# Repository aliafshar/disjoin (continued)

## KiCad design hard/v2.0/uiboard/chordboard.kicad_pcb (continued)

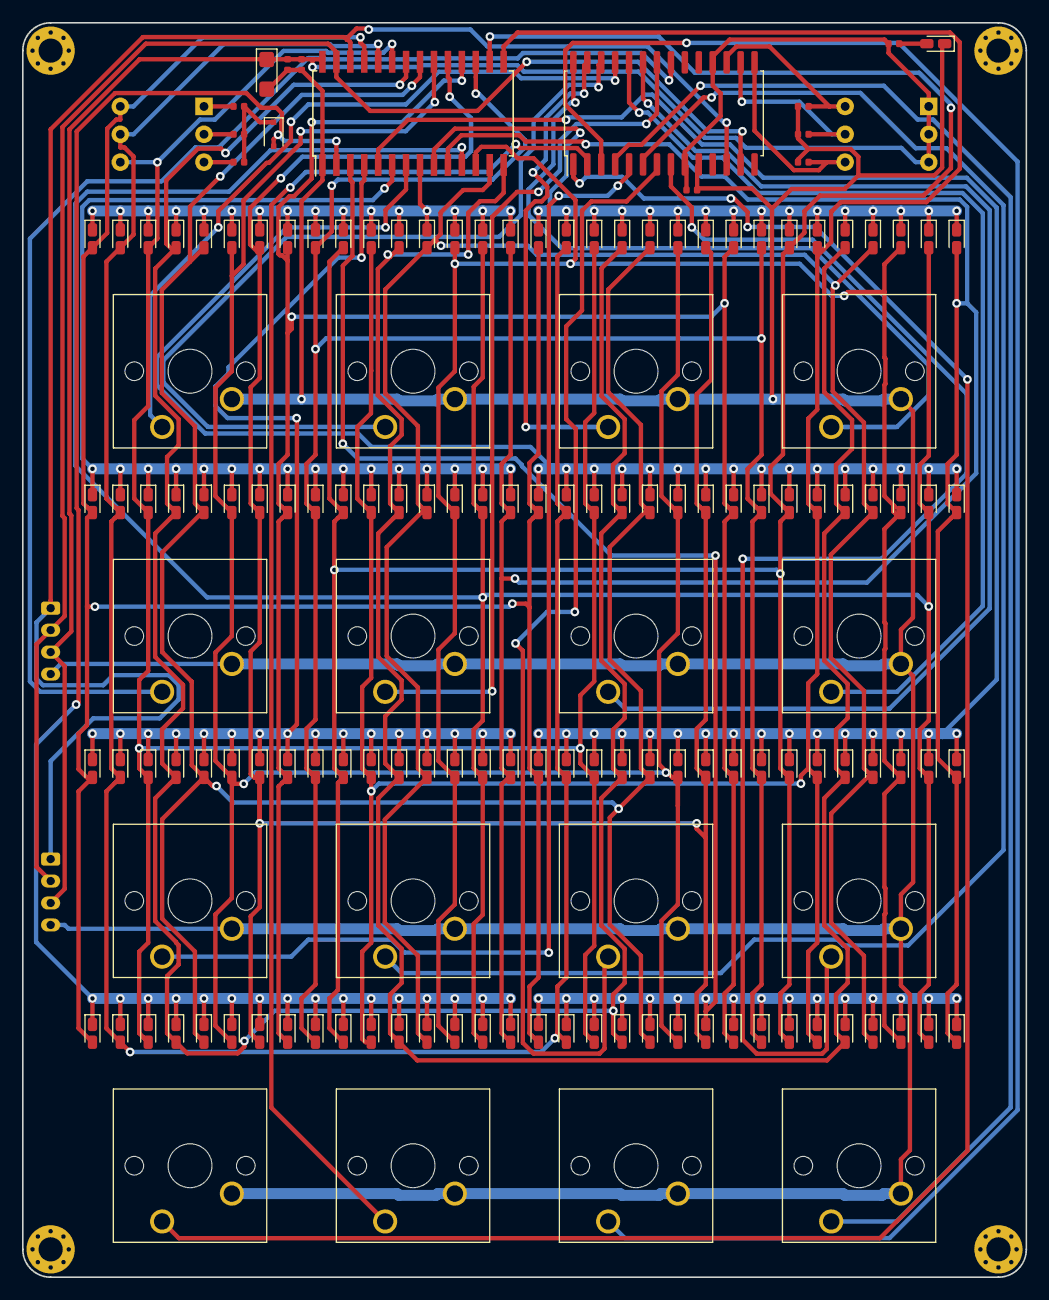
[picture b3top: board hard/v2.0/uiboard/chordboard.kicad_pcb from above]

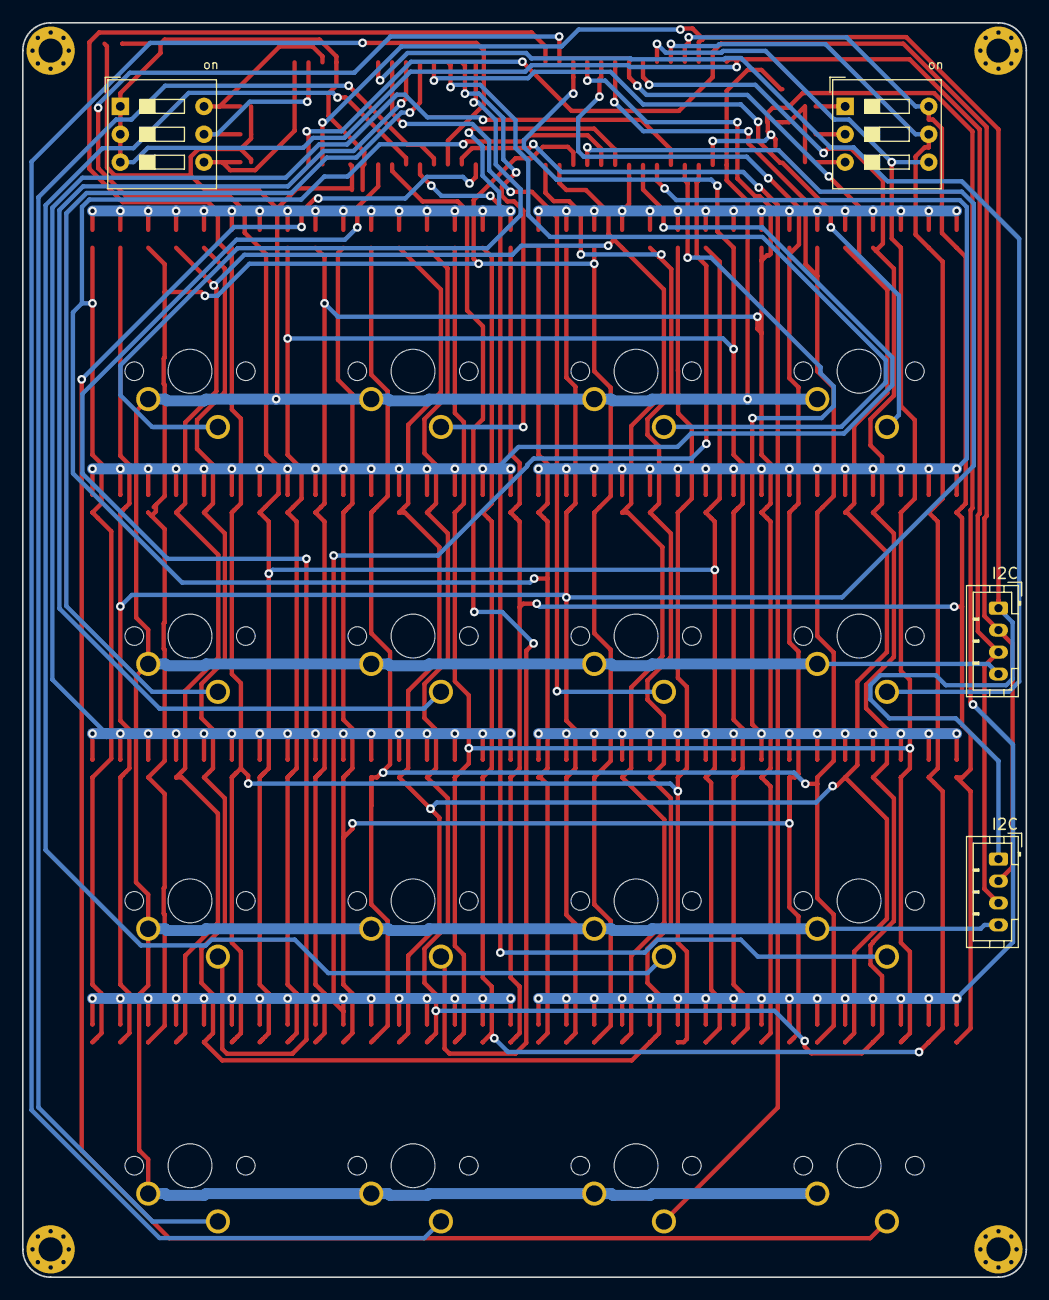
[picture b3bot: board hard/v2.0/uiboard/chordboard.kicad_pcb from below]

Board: 2 copper layers, 91.4 x 114.3 mm, 167 parts (4 on the bottom side), 52 nets.

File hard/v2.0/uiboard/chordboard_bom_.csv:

Component,Description,Part,References,Value,Footprint,Quantity Per PCB,Datasheet,LSCS
1,Polarized capacitor,CP_10uF,C4,CP_10uF,CP_EIA-3216-18_Kemet-A,1,~,C7171
2,Unpolarized capacitor,C_0.1uF,C1 C2 C3,C_0.1uF,C_0402_1005Metric,3,~,C1525
3,Diode,D_1N4148WS,D129,D_1N4148WS,D_SOD-323F,1,~,C2128
4,Light emitting diode,LED_RED,D1 D2 D3 D4 D5 D6 D7 D8 D9 D10 D11 D12 D13 D14 D15 D16 D17 D18 D19 D20 D21 D22 D23 D24 D25 D26 D27 D28 D29 D30 D31 D32 D33 D34 D35 D36 D37 D38 D39 D40 D41 D42 D43 D44 D45 D46 D47 D48 D49 D50 D51 D52 D53 D54 D55 D56 D57 D58 D59 D60 D61 D62 D63 D64 D65 D66 D67 D68 D69 D70 D71 D72 D73 D74 D75 D76 D77 D78 D79 D80 D81 D82 D83 D84 D85 D86 D87 D88 D89 D90 D91 D92 D93 D94 D95 D96 D97 D98 D99 D100 D101 D102 D103 D104 D105 D106 D107 D108 D109 D110 D111 D112 D113 D114 D115 D116 D117 D118 D119 D120 D121 D122 D123 D124 D125 D126 D127 D128 PLED1,LED_RED,LED_0603_1608Metric_Castellated,129,~,C2286
5,,HT16K33,HT1,HT16K33,SOIC-28W_7.5x17.9mm_P1.27mm,1,,C87502
6,Resistor,R_10K,R1 R2 R3 R4 R5 R6,R_10K,R_0402_1005Metric,6,~,C25744
7,Resistor,R_330R,R7,R_330R,R_0402_1005Metric,1,~,C25104
8,"16-bit I/O expander, I2C, interrupts, w pull-ups, SOIC-28",MCP23017_SO,U1,MCP23017_SO,SOIC-28W_7.5x17.9mm_P1.27mm,1,http://ww1.microchip.com/downloads/en/DeviceDoc/20001952C.pdf,C47023

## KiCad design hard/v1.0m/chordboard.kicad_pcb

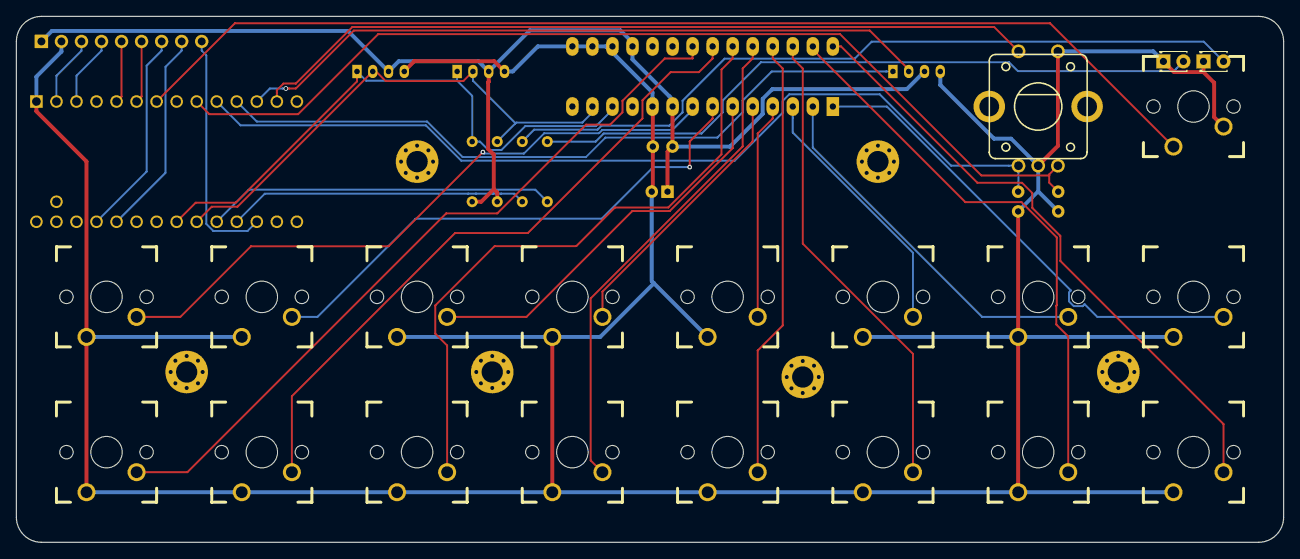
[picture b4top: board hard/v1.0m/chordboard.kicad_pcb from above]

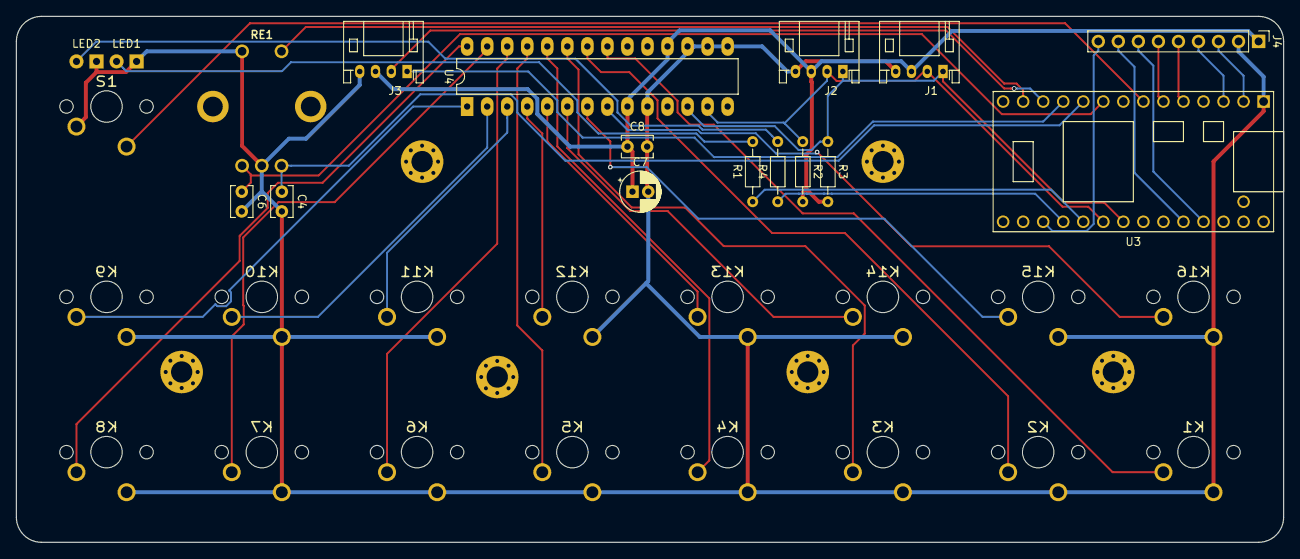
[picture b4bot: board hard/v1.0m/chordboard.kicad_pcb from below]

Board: 2 copper layers, 160.7 x 66.7 mm, 40 parts (14 on the bottom side), 37 nets.

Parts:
C4, C6, C8: C; C_Disc_D3.8mm_W2.6mm_P2.50mm
C7: CP; CP_Radial_D5.0mm_P2.00mm
J1, J2: GROVE_I2C; GROVE_I2C_ANGLED
J3: GROVE_UART; GROVE_I2C_ANGLED
J4: Conn_01x09_Male; PinHeader_1x09_P2.54mm_Vertical
K1, K2, K3, K4, K5, K6, K7, K8, K9, K10, K11, K12, K13, K14, K15, K16: KSW; CHERRY_PCB_100H
LED1, LED2: LED; LED_D1.8mm_W3.3mm_H2.4mm
MK1, MK2, MK3, MK4, MK5, MK6: Mounting_Hole
R1, R2, R3, R4: R; R_Axial_DIN0204_L3.6mm_D1.6mm_P7.62mm_Horizontal
RE1: ROTARY_ENCODER; Rotary_Encoder_BI_EN12-HS22AF30
S1: KSW; CHERRY_PCB_100H
U3: Teensy-LC; Teensy30_31_32_LC_EDGES
U4: MCP23017; DIP-28_W7.62mm_LongPads

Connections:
+3V3: C7.1, C8.1, J1.3, J2.3, J3.3, J4.1, R2.2, R3.2, U4.9, U4.18
/RE1A: C4.1, RE1.A, U3.10
/RE1B: C6.1, RE1.B, U3.9
/RE1S: RE1.SW1, U3.13
/RX1: J3.1, U3.11
/SCL: J1.1, J2.1, R3.1, U3.26, U4.12
/SDA: J1.2, J2.2, R2.1, U3.25, U4.13
/T1: J4.3, U3.2
/T2: J4.4, U3.3
/T3: J4.5, U3.5
/T4: J4.6, U3.6
/T5: J4.9, U3.22
/T6: J4.8, U3.29
/T7: J4.7, U3.30
/TX1: J3.2, U3.12
GND: C4.2, C6.2, C7.2, C8.2, J1.4, J2.4, J3.4, J4.2, K1.1, K2.1, K3.1, K4.1, K5.1, K6.1, K7.1, K8.1, K9.1, K10.1, K11.1, K12.1, K13.1, K14.1, K15.1, K16.1, LED1.1, LED2.1, RE1.C, RE1.SW2, S1.2, U3.1, U4.10, U4.15, U4.16, U4.17
unnamed: K1.2, U4.21
unnamed: K2.2, U4.22
unnamed: K3.2, U4.23
unnamed: K4.2, U4.24
unnamed: K5.2, U4.25
unnamed: K6.2, U4.26
unnamed: K7.2, U4.27
unnamed: K8.2, U4.28
unnamed: K9.2, U4.1
unnamed: K10.2, U4.2
unnamed: K11.2, U4.3
unnamed: K12.2, U4.4
unnamed: K13.2, U4.5
unnamed: K14.2, U4.6
unnamed: K15.2, U4.7
unnamed: K16.2, U4.8
unnamed: LED1.2, R1.2
unnamed: LED2.2, R4.2
unnamed: R1.1, U3.24
unnamed: R4.1, U3.23
unnamed: S1.1, U3.7

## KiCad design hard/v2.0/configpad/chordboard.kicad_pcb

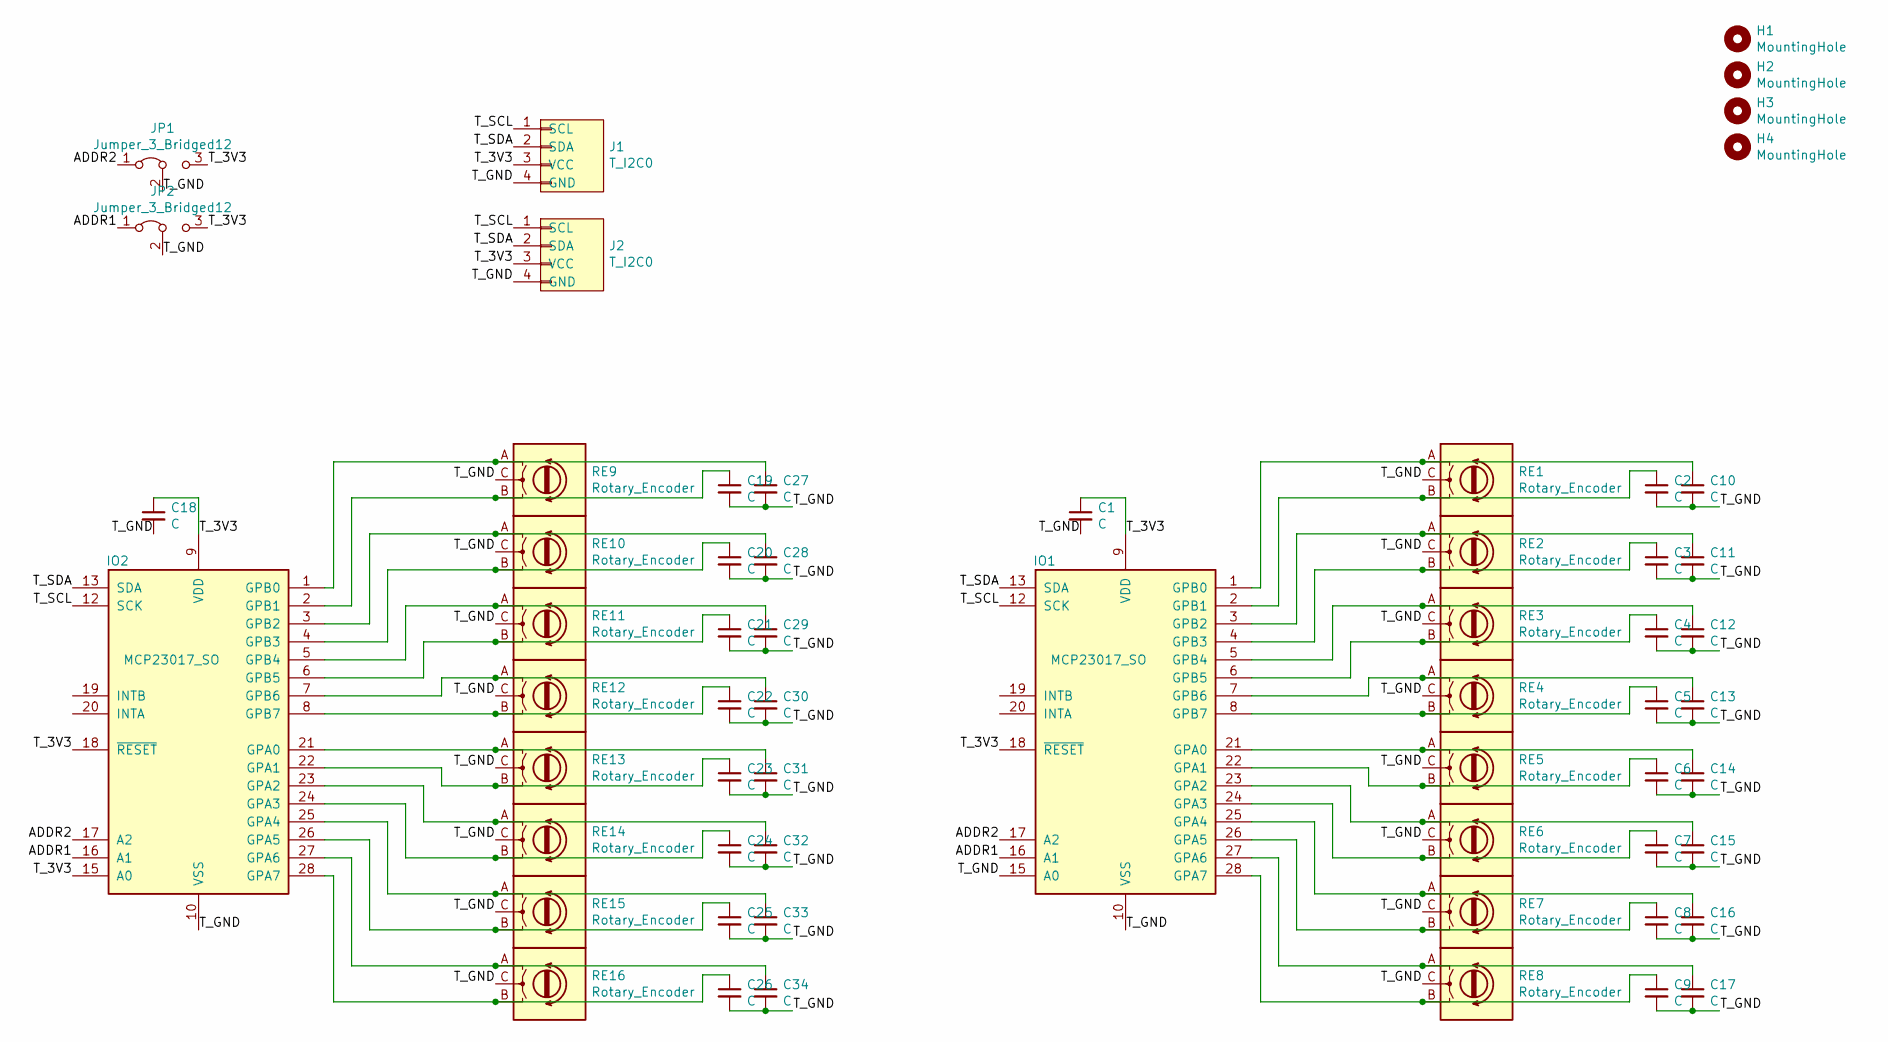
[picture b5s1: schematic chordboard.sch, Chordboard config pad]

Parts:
C1, C2, C3, C4, C5, C6, C7, C8, C9, C10, C11, C12, C13, C14, C15, C16, C17, C18, C19, C20, C21, C22, C23, C24, C25, C26, C27, C28, C29, C30, C31, C32, C33, C34: C; C_Disc_D3.4mm_W2.1mm_P2.50mm
H1, H2, H3, H4: MountingHole; MountingHole_2.7mm_M2.5_Pad_Via
IO1, IO2: MCP23017_SO; SOIC-28W_7.5x17.9mm_P1.27mm
J1, J2: T_I2C0; JST_PH_B4B-PH-K_1x04_P2.00mm_Vertical
JP1, JP2: Jumper_3_Bridged12; SolderJumper-3_P1.3mm_Bridged12_Pad1.0x1.5mm
RE1, RE2, RE3, RE4, RE5, RE6, RE7, RE8, RE9, RE10, RE11, RE12, RE13, RE14, RE15, RE16: Rotary_Encoder; RotaryEncoder_Alps_EC11E_Vertical_H20mm

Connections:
/ADDR1: IO1.16 (A1), IO2.16 (A1), JP2.1 (A)
/ADDR2: IO1.17 (A2), IO2.17 (A2), JP1.1 (A)
/T_3V3: C1.1, C18.1, IO1.9 (VDD), IO1.18 (~RESET~), IO2.9 (VDD), IO2.15 (A0), IO2.18 (~RESET~), J1.3 (VCC), J2.3 (VCC), JP1.3 (B), JP2.3 (B)
/T_GND: C1.2, C2.2, C3.2, C4.2, C5.2, C6.2, C7.2, C8.2, C9.2, C10.2, C11.2, C12.2, C13.2, C14.2, C15.2, C16.2, C17.2, C18.2, C19.2, C20.2, C21.2, C22.2, C23.2, C24.2, C25.2, C26.2, C27.2, C28.2, C29.2, C30.2, C31.2, C32.2, C33.2, C34.2, IO1.10 (VSS), IO1.15 (A0), IO2.10 (VSS), J1.4 (GND), J2.4 (GND), JP1.2 (C), JP2.2 (C), RE1.C, RE2.C, RE3.C, RE4.C, RE5.C, RE6.C, RE7.C, RE8.C, RE9.C, RE10.C, RE11.C, RE12.C, RE13.C, RE14.C, RE15.C, RE16.C
/T_SCL: IO1.12 (SCK), IO2.12 (SCK), J1.1 (SCL), J2.1 (SCL)
/T_SDA: IO1.13 (SDA), IO2.13 (SDA), J1.2 (SDA), J2.2 (SDA)
unnamed: C2.1, IO1.2 (GPB1), RE1.B
unnamed: C3.1, IO1.4 (GPB3), RE2.B
unnamed: C4.1, IO1.6 (GPB5), RE3.B
unnamed: C5.1, IO1.8 (GPB7), RE4.B
unnamed: C6.1, IO1.22 (GPA1), RE5.B
unnamed: C7.1, IO1.24 (GPA3), RE6.B
unnamed: C8.1, IO1.26 (GPA5), RE7.B
unnamed: C9.1, IO1.28 (GPA7), RE8.B
unnamed: C10.1, IO1.1 (GPB0), RE1.A
unnamed: C11.1, IO1.3 (GPB2), RE2.A
unnamed: C12.1, IO1.5 (GPB4), RE3.A
unnamed: C13.1, IO1.7 (GPB6), RE4.A
unnamed: C14.1, IO1.21 (GPA0), RE5.A
unnamed: C15.1, IO1.23 (GPA2), RE6.A
unnamed: C16.1, IO1.25 (GPA4), RE7.A
unnamed: C17.1, IO1.27 (GPA6), RE8.A
unnamed: C19.1, IO2.2 (GPB1), RE9.B
unnamed: C20.1, IO2.4 (GPB3), RE10.B
unnamed: C21.1, IO2.6 (GPB5), RE11.B
unnamed: C22.1, IO2.8 (GPB7), RE12.B
unnamed: C23.1, IO2.22 (GPA1), RE13.B
unnamed: C24.1, IO2.24 (GPA3), RE14.B
unnamed: C25.1, IO2.26 (GPA5), RE15.B
unnamed: C26.1, IO2.28 (GPA7), RE16.B
unnamed: C27.1, IO2.1 (GPB0), RE9.A
unnamed: C28.1, IO2.3 (GPB2), RE10.A
unnamed: C29.1, IO2.5 (GPB4), RE11.A
unnamed: C30.1, IO2.7 (GPB6), RE12.A
unnamed: C31.1, IO2.21 (GPA0), RE13.A
unnamed: C32.1, IO2.23 (GPA2), RE14.A
unnamed: C33.1, IO2.25 (GPA4), RE15.A
unnamed: C34.1, IO2.27 (GPA6), RE16.A

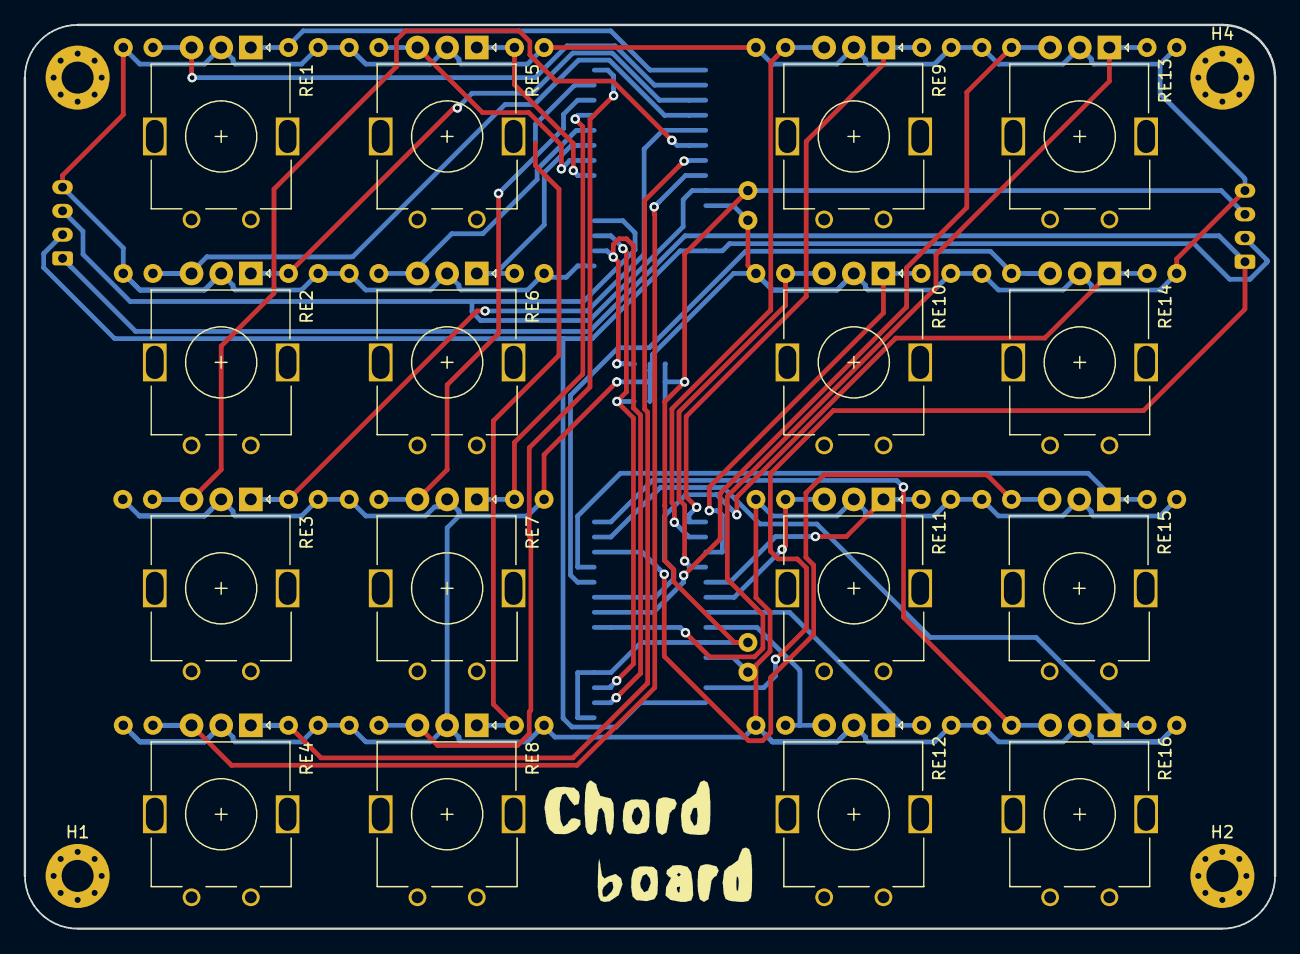
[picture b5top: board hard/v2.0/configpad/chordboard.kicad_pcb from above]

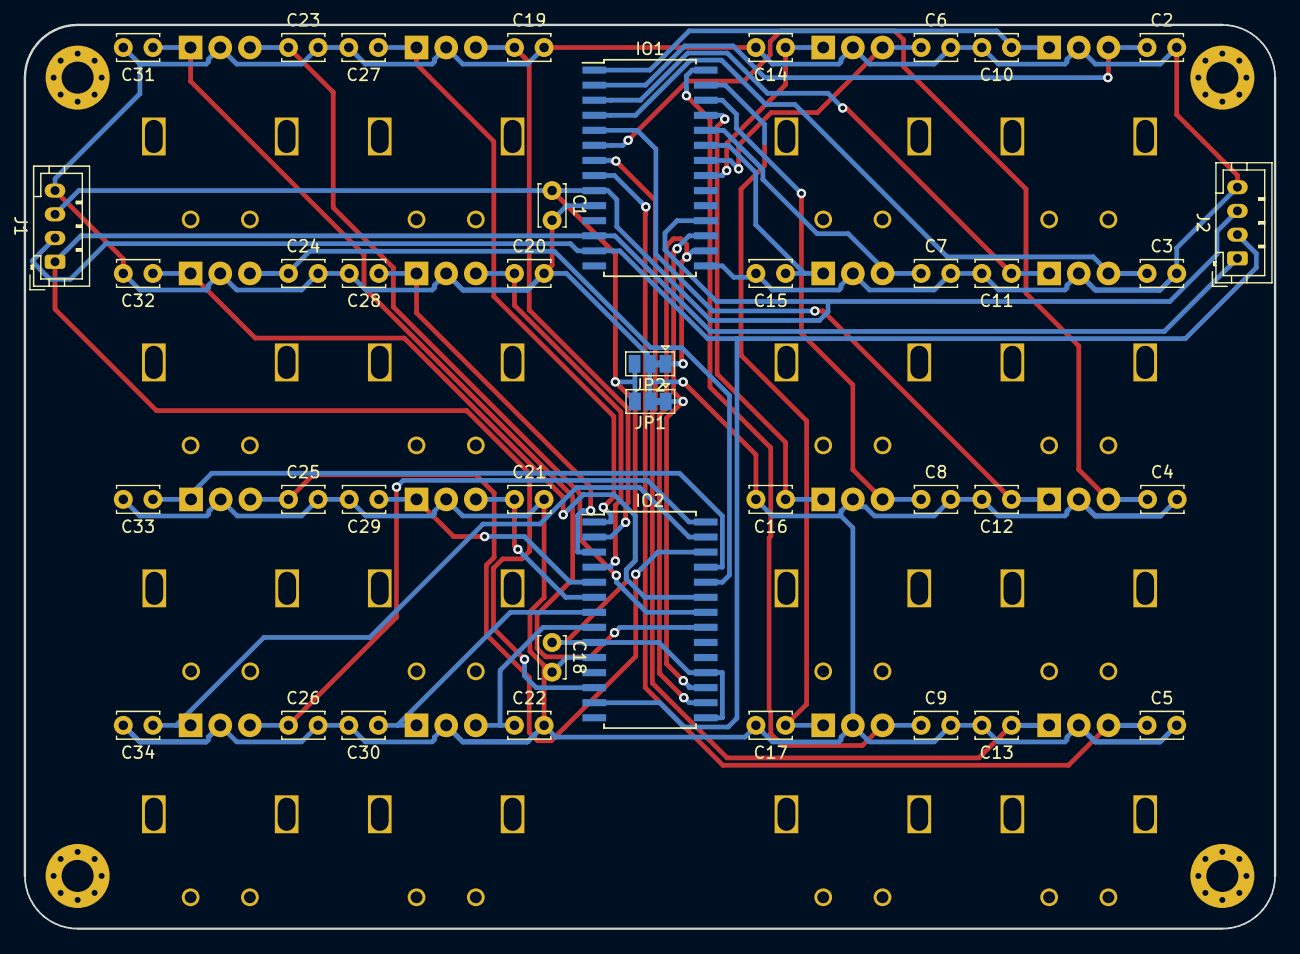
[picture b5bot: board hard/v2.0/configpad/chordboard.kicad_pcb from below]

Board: 2 copper layers, 105.4 x 76.2 mm, 60 parts (40 on the bottom side), 38 nets.

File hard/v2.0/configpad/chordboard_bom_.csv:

Component,Description,Part,References,Value,Footprint,Quantity Per PCB,Datasheet
1,"Unpolarized capacitor, small symbol",C_Small,C1 C2 C3 C4 C5 C6 C7 C8 C9 C10 C11 C12 C13 C14 C15 C16 C17 C18 C19 C20 C21 C22 C23 C24 C25 C26 C27 C28 C29 C30 C31 C32 C33 C34,C,C_Disc_D3.4mm_W2.1mm_P2.50mm,34,~
2,"16-bit I/O expander, I2C, interrupts, w pull-ups, SOIC-28",MCP23017_SO,IO1 IO2,MCP23017_SO,SOIC-28W_7.5x17.9mm_P1.27mm,2,http://ww1.microchip.com/downloads/en/DeviceDoc/20001952C.pdf
3,"Connector, single row, 01x04, pin header",GROVE_I2C,J1 J2,T_I2C0,JST_PH_B4B-PH-K_1x04_P2.00mm_Vertical,2,
4,"Jumper, 3-pole, pins 1+2 closed/bridged",Jumper_3_Bridged12,JP1 JP2,Jumper_3_Bridged12,SolderJumper-3_P1.3mm_Bridged12_Pad1.0x1.5mm,2,~
5,"Rotary encoder, dual channel, incremental quadrate outputs",Rotary_Encoder,RE1 RE2 RE3 RE4 RE5 RE6 RE7 RE8 RE9 RE10 RE11 RE12 RE13 RE14 RE15 RE16,Rotary_Encoder,RotaryEncoder_Alps_EC11E_Vertical_H20mm,16,~

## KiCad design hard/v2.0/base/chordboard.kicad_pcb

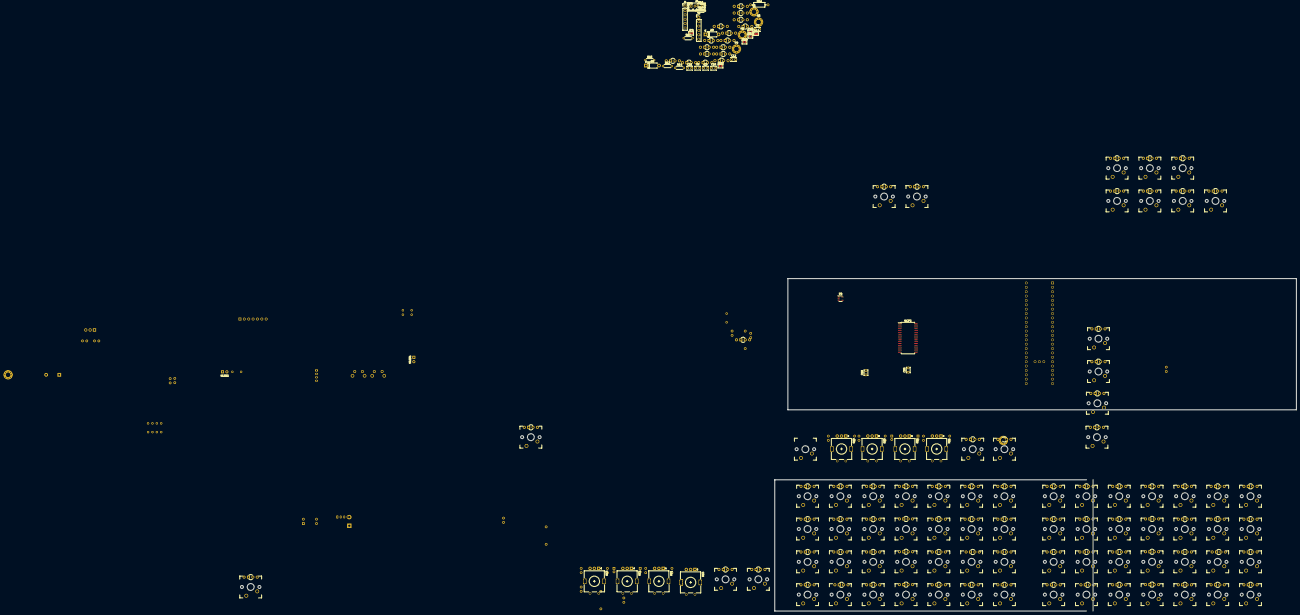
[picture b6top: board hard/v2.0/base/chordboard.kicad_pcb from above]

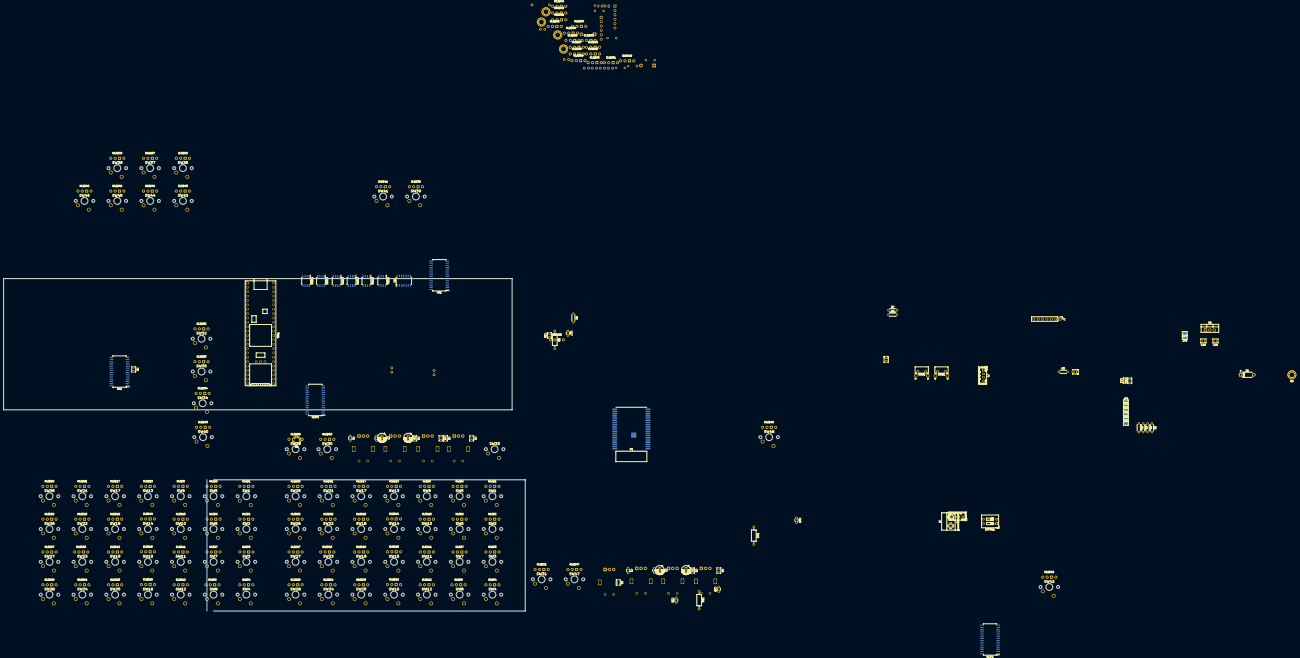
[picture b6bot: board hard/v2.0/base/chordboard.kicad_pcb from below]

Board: 2 copper layers, 278 parts (70 on the bottom side), 147 nets, no tracks yet.

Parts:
C1, C1#2, C2, C2#2, C17, C18, C22, C23: C; C_Disc_D3.0mm_W1.6mm_P2.50mm
C3, C3#2: 10uF; CP_Radial_D5.0mm_P2.00mm
C4, C4#2: 100uF; CP_Radial_D5.0mm_P2.00mm
C5, C5#2, C5#3, C5#4, C6, C6#2, C6#3, C6#4, C7, C8, C9, C10, C11, C12, C13, C14, C15, C16, C19, C20, C21: C_Small; C_Disc_D3.0mm_W2.0mm_P2.50mm
D1, D2, D3: D; D_DO-41_SOD81_P7.62mm_Horizontal
DIPSW1: E_BOOTOPTS; SW_DIP_SPSTx02_Slide_9.78x7.26mm_W7.62mm_P2.54mm
H1, H2, H3, H4, H5, H6: MountingHole; MountingHole_2.7mm_M2.5_Pad_Via
HLED1: E_HEARTBEAT; LED_D1.8mm_W3.3mm_H2.4mm
HLED2: T_HEARTBEAT; LED_D1.8mm_W3.3mm_H2.4mm
HT1, HT2: HT16K33; SOIC-28W_7.5x17.9mm_P1.27mm
J1: T_UART0; PinHeader_1x06_P2.54mm_Vertical
J2: E_I2C0; JST_PH_B4B-PH-K_1x04_P2.00mm_Vertical
J3: E_UART0; PinHeader_1x06_P2.54mm_Vertical
J4: T_UART5; JST_PH_B4B-PH-K_1x04_P2.00mm_Vertical
J5: T_I2C0; JST_PH_B4B-PH-K_1x04_P2.00mm_Vertical
J6: ++5V_IN; TerminalBlock_Phoenix_MKDS-1,5-2_1x02_P5.00mm_Horizontal
J7: Conn_01x07; PinHeader_1x07_P2.54mm_Vertical
JP1: J_ESP_RX2; SolderJumper-2_P1.3mm_Bridged2Bar_Pad1.0x1.5mm
JP2: J_ESP_TX2; SolderJumper-2_P1.3mm_Bridged2Bar_Pad1.0x1.5mm
JP3: J_ESP_RST; SolderJumper-2_P1.3mm_Bridged2Bar_Pad1.0x1.5mm
JP4: J_ESP_D0; SolderJumper-2_P1.3mm_Bridged2Bar_Pad1.0x1.5mm
JP5: J_ESP_3V3; SolderJumper-2_P1.3mm_Bridged2Bar_Pad1.0x1.5mm
JP6: Jumper_2_Bridged; SolderJumper-2_P1.3mm_Bridged2Bar_Pad1.0x1.5mm
JP7: J_PWR_3V3; SolderJumper-2_P1.3mm_Bridged2Bar_Pad1.0x1.5mm
JP8: J_PWR_GND; SolderJumper-2_P1.3mm_Bridged2Bar_Pad1.0x1.5mm
JP9, JP10, JP11, JP13, JP14: J_HT_AD; SolderJumper-2_P1.3mm_Open_Pad1.0x1.5mm
JP12: J_HT_AD; SolderJumper-2_P1.3mm_Bridged2Bar_Pad1.0x1.5mm
KLED1, KLED1#2, KLED2, KLED2#2, KLED3, KLED3#2, KLED4, KLED4#2, KLED5, KLED5#2, KLED6, KLED6#2, KLED7, KLED7#2, KLED8, KLED8#2, KLED9, KLED9#2, KLED10, KLED10#2, KLED11, KLED11#2, KLED12, KLED12#2, KLED13, KLED13#2, KLED14, KLED14#2, KLED15, KLED15#2, KLED16, KLED16#2, KLED17, KLED17#2, KLED18, KLED18#2, KLED19, KLED19#2, KLED20, KLED20#2, KLED21, KLED21#2, KLED22, KLED22#2, KLED23, KLED23#2, KLED24, KLED24#2, KLED25, KLED25#2, KLED26, KLED26#2, KLED27, KLED27#2, KLED28, KLED28#2, KLED29, KLED30, KLED31, KLED32, KLED33, KLED34, KLED35, KLED36, KLED37, KLED38, KLED39, KLED40, KLED41, KLED42, KLED43, KLED44, KLED45, KLED46, KLED47, KLED48, KLED49, KLED50, KLED51, KLED52, KLED53, KLED54, KLED55, KLED56, KLED57, KLED58, KLED59, KLED60, KLED61, KLED62, KLED63, KLED64: LED_ARGB; LED_D3.0mm-4
MCP1, MCP2, MCP3: MCP23017_SP; SOIC-28W_7.5x17.9mm_P1.27mm
MEM1, MEM2, MEM3, MEM4, MEM5, MEM6: 23LC1024; SOIC-8_3.9x4.9mm_P1.27mm
R1, R6, R13, R14, R15, R16, R17, R18: 10K; R_Axial_DIN0204_L3.6mm_D1.6mm_P5.08mm_Horizontal
R2, R3: 200; R_Axial_DIN0204_L3.6mm_D1.6mm_P5.08mm_Horizontal
R4, R5, R7, R8: 4.7K; R_Axial_DIN0204_L3.6mm_D1.6mm_P5.08mm_Horizontal
R9, R10, R11, R12: R; R_Axial_DIN0207_L6.3mm_D2.5mm_P10.16mm_Horizontal
RE1, RE1#2, RE2, RE2#2, RE3, RE3#2, RE3#3, RE3#4: Rotary_Encoder; RotaryEncoder_Alps_EC11E_Vertical_H20mm
RSW1: E_PGM; SW_Tactile_SPST_Angled_PTS645Vx58-2LFS
RSW2: T_PGM; SW_Tactile_SPST_Angled_PTS645Vx58-2LFS
SW1, SW1#2, SW2, SW2#2, SW3, SW3#2, SW4, SW4#2, SW5, SW5#2, SW6, SW6#2, SW7, SW7#2, SW8, SW8#2, SW9, SW9#2, SW10, SW10#2, SW11, SW11#2, SW12, SW12#2, SW13, SW13#2, SW14, SW14#2, SW15, SW15#2, SW16, SW16#2, SW17, SW17#2, SW18, SW18#2, SW19, SW19#2, SW20, SW20#2, SW21, SW21#2, SW22, SW22#2, SW23, SW23#2, SW24, SW24#2, SW25, SW25#2, SW26, SW26#2, SW27, SW27#2, SW28, SW28#2, SW29, SW30, SW31, SW32, SW33, SW34, SW35, SW36, SW37, SW38, SW39, SW40, SW41, SW42, SW43, SW44, SW45, SW46, SW47, SW48: SW_Push; CHERRY_PCB_100H
TEE1: Teensy3.6; teensy36
U1: ESP32-WROVER
U2: AZ1117-3.3; TO-220-3_Vertical
U3: 74LS126; SOIC-14_3.9x8.7mm_P1.27mm
U4: MCP73832-2-OT; SOT-23-5

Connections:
+3V3: C4.1, C4#2.1, C5.1, C5#2.1, C5#3.1, C5#4.1, C6.1, C6#2.1, C6#3.1, C6#4.1, C7.1, C8.1, C9.1, C10.1, C19.1, C20.1, C21.1, J4.3, J5.3, JP5.1, JP7.1, JP7.2, MCP1.9, MCP1.16, MCP1.18, MCP2.9, MCP2.18, MCP3.9, MCP3.17, MCP3.18, MEM1.3, MEM1.7, MEM1.8, MEM2.3, MEM2.7, MEM2.8, MEM3.3, MEM3.7, MEM3.8, MEM4.3, MEM4.7, MEM4.8, MEM5.3, MEM5.7, MEM5.8, MEM6.3, MEM6.7, MEM6.8, R7.2, R8.2, R9.1, R10.1, TEE1.15, U2.2
+5V: C3.1, C3#2.1, D1.1, U2.3
/COM_AD1: D2.2, HT2.2, KLED1.4, KLED1#2.4, KLED2.4, KLED2#2.4, KLED3.4, KLED3#2.4, KLED4.4, KLED4#2.4, KLED5.4, KLED5#2.4, KLED6.4, KLED6#2.4, KLED7.4, KLED7#2.4, KLED8.4, KLED8#2.4, KLED9.4, KLED9#2.4, KLED10.4, KLED10#2.4, KLED11.4, KLED11#2.4, KLED12.4, KLED12#2.4, KLED13.4, KLED13#2.4, KLED14.4, KLED14#2.4, KLED15.4, KLED15#2.4, KLED16.4, KLED16#2.4
/COM_AD2: D3.2, HT1.2, KLED33.4, KLED34.4, KLED35.4, KLED36.4, KLED37.4, KLED38.4, KLED39.4, KLED40.4, KLED41.4, KLED42.4, KLED43.4, KLED44.4, KLED45.4, KLED46.4, KLED47.4, KLED48.4
/ESP_3V3: C1.1, C1#2.1, C2.1, C2#2.1, J2.3, JP5.2, R1.2, R4.2, R5.2, R6.1, U1.2
/ESP_D0: DIPSW1.2, JP4.2, R6.2, U1.25
/ESP_GND: C1.2, C1#2.2, C2.2, C2#2.2, DIPSW1.3, DIPSW1.4, HLED1.1, J2.4, J3.1, JP6.2, U1.1, U1.15, U1.38
/ESP_RST: DIPSW1.1, JP3.2, R1.1, U1.3
/ESP_RX0: J3.4, U1.34
/ESP_RX2: JP1.2, U1.14
/ESP_SCL: J2.1, R4.1, U1.36
/ESP_SDA: J2.2, R5.1, U1.33
/ESP_TX0: J3.5, U1.35
/ESP_TX2: JP2.2, U1.16
/MEMCARD_CS1: J7.1, MEM1.1, TEE1.4
/MEMCARD_CS2: J7.2, MEM2.1, TEE1.5
/MEMCARD_CS3: J7.3, MEM3.1, TEE1.6
/MEMCARD_CS4: J7.4, MEM4.1, MEM5.1, MEM6.1, TEE1.7
/MEMCARD_MISO: J7.6, MEM1.2, MEM2.2, MEM3.2, MEM4.2, MEM5.2, MEM6.2, TEE1.14
/MEMCARD_MOSI: J7.5, MEM1.5, MEM2.5, MEM3.5, MEM4.5, MEM5.5, MEM6.5, TEE1.9
/MEMCARD_SCK: J7.7, MEM1.6, MEM2.6, MEM3.6, MEM4.6, MEM5.6, MEM6.6, TEE1.36
/RE1A: C11.1, RE1.A, RE1#2.A, TEE1.30
/RE1B: C12.1, RE1.B, RE1#2.B, TEE1.29
/RE2A: C13.1, RE2.A, RE2#2.A, TEE1.28
/RE2B: C14.1, RE2.B, RE2#2.B, TEE1.27
/RE3A: C15.1, RE3.A, RE3#2.A, RE3#3.A, RE3#4.A, TEE1.39
/RE3B: C16.1, RE3.B, RE3#2.B, RE3#3.B, RE3#4.B, TEE1.38
/SCL5: HT1.26, HT2.26, R12.2
/SDA5: HT1.27, HT2.27, R11.2
/T_5V: C17.2, C18.2, C22.2, C23.2, HT1.28, HT2.28, R11.1, R12.1, TEE1.48
/T_GND: C5.2, C5#2.2, C5#3.2, C5#4.2, C6.2, C6#2.2, C6#3.2, C6#4.2, C7.2, C8.2, C9.2, C10.2, C11.2, C12.2, C13.2, C14.2, C15.2, C16.2, C17.1, C18.1, C19.2, C20.2, C21.2, C22.1, C23.1, HLED2.1, HT1.1, HT2.1, J1.1, J4.4, J5.4, JP6.1, JP8.2, MCP1.10, MCP1.15, MCP1.17, MCP2.10, MCP2.15, MCP2.16, MCP2.17, MCP3.10, MCP3.15, MCP3.16, MEM1.4, MEM2.4, MEM3.4, MEM4.4, MEM5.4, MEM6.4, RE1.C, RE1#2.C, RE2.C, RE2#2.C, RE3.C, RE3#2.C, RE3#3.C, RE3#4.C, RSW1.2, RSW2.1, SW1.2, SW1#2.2, SW2.2, SW2#2.2, SW3.2, SW3#2.2, SW4.2, SW4#2.2, SW5.2, SW5#2.2, SW6.2, SW6#2.2, SW7.2, SW7#2.2, SW8.2, SW8#2.2, SW9.2, SW9#2.2, SW10.2, SW10#2.2, SW11.2, SW11#2.2, SW12.2, SW12#2.2, SW13.2, SW13#2.2, SW14.2, SW14#2.2, SW15.2, SW15#2.2, SW16.2, SW16#2.2, SW17.2, SW17#2.2, SW18.2, SW18#2.2, SW19.2, SW19#2.2, SW20.2, SW20#2.2, SW21.2, SW21#2.2, SW22.2, SW22#2.2, SW23.2, SW23#2.2, SW24.2, SW24#2.2, SW25.2, SW25#2.2, SW26.2, SW26#2.2, SW27.2, SW27#2.2, SW28.2, SW28#2.2, SW29.2, SW30.2, SW31.2, SW32.2, SW33.2, SW34.2, SW35.2, SW36.2, SW37.2, SW38.2, SW39.2, SW40.2, SW41.2, SW42.2, SW43.2, SW44.2, SW45.2, SW46.2, SW47.2, SW48.2, TEE1.1
/T_PGM: RSW2.2, TEE1.51
/T_RX1: J1.4, TEE1.2
/T_RX4: JP2.1, TEE1.23
/T_SCL: J5.1, MCP1.12, MCP2.12, MCP3.12, R7.1, R9.2, TEE1.41
/T_SDA: J5.2, MCP1.13, MCP2.13, MCP3.13, R8.1, R10.2, TEE1.40
/T_TX1: J1.5, TEE1.3
/T_TX4: JP1.1, TEE1.24
GND: C3.2, C3#2.2, C4.2, C4#2.2, J6.2, JP8.1, U2.1
unnamed: D1.2, J6.1
unnamed: D2.1, R13.2, R14.2, R15.2
unnamed: D3.1, R16.2, R17.2, R18.2
unnamed: HLED1.2, R2.2
unnamed: HLED2.2, R3.2
unnamed: HT1.3, KLED33.3, KLED34.3, KLED35.3, KLED36.3, KLED37.3, KLED38.3, KLED39.3, KLED40.3, KLED41.3, KLED42.3, KLED43.3, KLED44.3, KLED45.3, KLED46.3, KLED47.3, KLED48.3
unnamed: HT1.4, KLED33.2, KLED34.2, KLED35.2, KLED36.2, KLED37.2, KLED38.2, KLED39.2, KLED40.2, KLED41.2, KLED42.2, KLED43.2, KLED44.2, KLED45.2, KLED46.2, KLED47.2, KLED48.2
unnamed: HT1.5, KLED49.4, KLED50.4, KLED51.4, KLED52.4, KLED53.4, KLED54.4, KLED55.4, KLED56.4, KLED57.4, KLED58.4, KLED59.4, KLED60.4, KLED61.4, KLED62.4, KLED63.4, KLED64.4
unnamed: HT1.6, KLED49.3, KLED50.3, KLED51.3, KLED52.3, KLED53.3, KLED54.3, KLED55.3, KLED56.3, KLED57.3, KLED58.3, KLED59.3, KLED60.3, KLED61.3, KLED62.3, KLED63.3, KLED64.3
unnamed: HT1.7, KLED49.2, KLED50.2, KLED51.2, KLED52.2, KLED53.2, KLED54.2, KLED55.2, KLED56.2, KLED57.2, KLED58.2, KLED59.2, KLED60.2, KLED61.2, KLED62.2, KLED63.2, KLED64.2
unnamed: HT1.10, KLED48.1, KLED64.1
unnamed: HT1.11, KLED47.1, KLED63.1
unnamed: HT1.12, KLED46.1, KLED62.1
unnamed: HT1.13, KLED45.1, KLED61.1
unnamed: HT1.14, KLED44.1, KLED60.1
unnamed: HT1.15, KLED43.1, KLED59.1
unnamed: HT1.16, KLED42.1, KLED58.1
unnamed: HT1.17, KLED41.1, KLED57.1
unnamed: HT1.18, KLED40.1, KLED56.1
unnamed: HT1.19, KLED39.1, KLED55.1
unnamed: HT1.20, KLED38.1, KLED54.1
unnamed: HT1.21, KLED37.1, KLED53.1
unnamed: HT1.22, KLED36.1, KLED52.1
unnamed: HT1.23, JP12.2, KLED35.1, KLED51.1
unnamed: HT1.24, JP13.2, KLED34.1, KLED50.1
unnamed: HT1.25, JP14.2, KLED33.1, KLED49.1
unnamed: HT2.3, KLED1.3, KLED1#2.3, KLED2.3, KLED2#2.3, KLED3.3, KLED3#2.3, KLED4.3, KLED4#2.3, KLED5.3, KLED5#2.3, KLED6.3, KLED6#2.3, KLED7.3, KLED7#2.3, KLED8.3, KLED8#2.3, KLED9.3, KLED9#2.3, KLED10.3, KLED10#2.3, KLED11.3, KLED11#2.3, KLED12.3, KLED12#2.3, KLED13.3, KLED13#2.3, KLED14.3, KLED14#2.3, KLED15.3, KLED15#2.3, KLED16.3, KLED16#2.3
unnamed: HT2.4, KLED1.2, KLED1#2.2, KLED2.2, KLED2#2.2, KLED3.2, KLED3#2.2, KLED4.2, KLED4#2.2, KLED5.2, KLED5#2.2, KLED6.2, KLED6#2.2, KLED7.2, KLED7#2.2, KLED8.2, KLED8#2.2, KLED9.2, KLED9#2.2, KLED10.2, KLED10#2.2, KLED11.2, KLED11#2.2, KLED12.2, KLED12#2.2, KLED13.2, KLED13#2.2, KLED14.2, KLED14#2.2, KLED15.2, KLED15#2.2, KLED16.2, KLED16#2.2
unnamed: HT2.5, KLED17.4, KLED17#2.4, KLED18.4, KLED18#2.4, KLED19.4, KLED19#2.4, KLED20.4, KLED20#2.4, KLED21.4, KLED21#2.4, KLED22.4, KLED22#2.4, KLED23.4, KLED23#2.4, KLED24.4, KLED24#2.4, KLED25.4, KLED25#2.4, KLED26.4, KLED26#2.4, KLED27.4, KLED27#2.4, KLED28.4, KLED28#2.4, KLED29.4, KLED30.4, KLED31.4, KLED32.4
unnamed: HT2.6, KLED17.3, KLED17#2.3, KLED18.3, KLED18#2.3, KLED19.3, KLED19#2.3, KLED20.3, KLED20#2.3, KLED21.3, KLED21#2.3, KLED22.3, KLED22#2.3, KLED23.3, KLED23#2.3, KLED24.3, KLED24#2.3, KLED25.3, KLED25#2.3, KLED26.3, KLED26#2.3, KLED27.3, KLED27#2.3, KLED28.3, KLED28#2.3, KLED29.3, KLED30.3, KLED31.3, KLED32.3
unnamed: HT2.7, KLED17.2, KLED17#2.2, KLED18.2, KLED18#2.2, KLED19.2, KLED19#2.2, KLED20.2, KLED20#2.2, KLED21.2, KLED21#2.2, KLED22.2, KLED22#2.2, KLED23.2, KLED23#2.2, KLED24.2, KLED24#2.2, KLED25.2, KLED25#2.2, KLED26.2, KLED26#2.2, KLED27.2, KLED27#2.2, KLED28.2, KLED28#2.2, KLED29.2, KLED30.2, KLED31.2, KLED32.2
unnamed: HT2.10, KLED16.1, KLED16#2.1, KLED32.1
unnamed: HT2.11, KLED15.1, KLED15#2.1, KLED31.1
unnamed: HT2.12, KLED14.1, KLED14#2.1, KLED30.1
unnamed: HT2.13, KLED13.1, KLED13#2.1, KLED29.1
unnamed: HT2.14, KLED12.1, KLED12#2.1, KLED28.1, KLED28#2.1
unnamed: HT2.15, KLED11.1, KLED11#2.1, KLED27.1, KLED27#2.1
unnamed: HT2.16, KLED10.1, KLED10#2.1, KLED26.1, KLED26#2.1
unnamed: HT2.17, KLED9.1, KLED9#2.1, KLED25.1, KLED25#2.1
unnamed: HT2.18, KLED8.1, KLED8#2.1, KLED24.1, KLED24#2.1
unnamed: HT2.19, KLED7.1, KLED7#2.1, KLED23.1, KLED23#2.1
unnamed: HT2.20, KLED6.1, KLED6#2.1, KLED22.1, KLED22#2.1
unnamed: HT2.21, KLED5.1, KLED5#2.1, KLED21.1, KLED21#2.1
unnamed: HT2.22, KLED4.1, KLED4#2.1, KLED20.1, KLED20#2.1
unnamed: HT2.23, JP9.2, KLED3.1, KLED3#2.1, KLED19.1, KLED19#2.1
unnamed: HT2.24, JP10.2, KLED2.1, KLED2#2.1, KLED18.1, KLED18#2.1
unnamed: HT2.25, JP11.2, KLED1.1, KLED1#2.1, KLED17.1, KLED17#2.1
unnamed: J4.1, TEE1.26
unnamed: J4.2, TEE1.25
unnamed: JP3.1, TEE1.17
unnamed: JP4.1, TEE1.18
unnamed: JP9.1, R13.1
unnamed: JP10.1, R14.1
unnamed: JP11.1, R15.1
unnamed: JP12.1, R16.1
unnamed: JP13.1, R17.1
unnamed: JP14.1, R18.1
unnamed: MCP1.1, SW1.1, SW1#2.1
unnamed: MCP1.2, SW2.1, SW2#2.1
unnamed: MCP1.3, SW3.1, SW3#2.1
unnamed: MCP1.4, SW4.1, SW4#2.1
unnamed: MCP1.5, SW5.1, SW5#2.1
unnamed: MCP1.6, SW6.1, SW6#2.1
unnamed: MCP1.7, SW7.1, SW7#2.1
unnamed: MCP1.8, SW8.1, SW8#2.1
unnamed: MCP1.21, SW9.1, SW9#2.1
unnamed: MCP1.22, SW10.1, SW10#2.1
unnamed: MCP1.23, SW11.1, SW11#2.1
unnamed: MCP1.24, SW12.1, SW12#2.1
unnamed: MCP1.25, SW13.1, SW13#2.1
unnamed: MCP1.26, SW14.1, SW14#2.1
unnamed: MCP1.27, SW15.1, SW15#2.1
unnamed: MCP1.28, SW16.1, SW16#2.1
unnamed: MCP2.1, SW17.1, SW17#2.1
unnamed: MCP2.2, SW18.1, SW18#2.1
unnamed: MCP2.3, SW19.1, SW19#2.1
unnamed: MCP2.4, SW20.1, SW20#2.1
unnamed: MCP2.5, SW21.1, SW21#2.1
unnamed: MCP2.6, SW22.1, SW22#2.1
unnamed: MCP2.7, SW23.1, SW23#2.1
unnamed: MCP2.8, SW24.1, SW24#2.1
unnamed: MCP2.21, SW25.1, SW25#2.1
unnamed: MCP2.22, SW26.1, SW26#2.1
unnamed: MCP2.23, SW27.1, SW27#2.1
unnamed: MCP2.24, SW28.1, SW28#2.1
unnamed: MCP2.25, SW29.1
unnamed: MCP2.26, SW30.1
unnamed: MCP2.27, SW31.1
unnamed: MCP2.28, SW32.1
unnamed: MCP3.1, SW33.1
unnamed: MCP3.2, SW34.1
unnamed: MCP3.3, SW35.1
unnamed: MCP3.4, SW36.1
unnamed: MCP3.5, SW37.1
unnamed: MCP3.6, SW38.1
unnamed: MCP3.7, SW39.1
unnamed: MCP3.8, SW40.1
unnamed: MCP3.21, SW41.1
unnamed: MCP3.22, SW42.1
unnamed: MCP3.23, SW43.1
unnamed: MCP3.24, SW44.1
unnamed: MCP3.25, SW45.1
unnamed: MCP3.26, SW46.1
unnamed: MCP3.27, SW47.1
unnamed: MCP3.28, SW48.1
unnamed: R2.1, U1.13
unnamed: R3.1, TEE1.43
unnamed: RSW1.1, TEE1.16
